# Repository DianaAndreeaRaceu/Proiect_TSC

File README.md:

# InkTime - Hardware Design

## Overview

Acest repository contine partea hardware pentru proiectul InkTime, realizat in Fusion 360 Electronics in jurul microcontroller-ului nRF52840.

Dispozitivul include:
- microcontroller nRF52840
- alimentare din baterie Li-Po
- incarcare prin USB-C
- fuel gauge pentru monitorizarea bateriei
- convertor DC/DC
- display E-Paper
- IMU
- driver haptic
- interfata SWD pentru programare si debug

Scopul proiectului a fost realizarea schemei electrice, a PCB-ului, a fisierelor de fabricatie si a documentatiei tehnice pentru review.

---

## Block Diagram

Diagrama bloc a proiectului este inclusa in folderul Images.

Pe scurt, sistemul functioneaza astfel:
USB-C asigura alimentarea si incarcarea bateriei.
BQ25180 gestioneaza partea de charging si power-path.
RT6160 genereaza rail-ul necesar pentru logica sistemului.
MAX17048 masoara starea bateriei.
nRF52840 este controlerul principal.
Display-ul E-Paper este controlat de microcontroller prin semnale dedicate.
IMU-ul si DRV2605 sunt conectate la MCU prin I2C si GPIO-uri de control.
Antena si reteaua de matching asigura partea RF pentru nRF52840.

---

## Repository Structure

Repository-ul este organizat astfel:

Hardware contine fisierele de schema si PCB.  
Manufacturing contine fisierele Gerber, BOM si CPL.  
Mechanical este rezervat pentru fisiere mecanice, daca este cazul.  
Images contine capturi, randari si diagrama bloc.  
README.md contine documentatia proiectului.  
LICENSE contine licenta open-source.

---

## BOM

Componentele principale folosite in proiect sunt urmatoarele:

Microcontrollerul principal este nRF52840. Acesta gestioneaza toate functiile dispozitivului, inclusiv controlul display-ului, comunicatia cu perifericele, debug-ul si partea RF. Componenta poate fi cautata pe JLCPCB dupa “nRF52840”, iar datasheet-ul oficial este disponibil pe site-ul Nordic Semiconductor.

Circuitul de incarcare si power-path este BQ25180YBGR. Acesta gestioneaza incarcarea bateriei Li-Po si distributia alimentarii in sistem. Componenta poate fi cautata pe JLCPCB dupa “BQ25180”, iar datasheet-ul este disponibil pe site-ul Texas Instruments.

Convertorul DC/DC este RT6160AWSC. Acesta genereaza rail-ul principal de alimentare pentru logica placii. Componenta poate fi cautata pe JLCPCB dupa “RT6160”, iar datasheet-ul este disponibil pe site-ul Richtek.

Fuel gauge-ul este MAX17048G+T10. Acesta monitorizeaza starea bateriei si furnizeaza informatii utile pentru firmware. Componenta poate fi cautata pe JLCPCB dupa “MAX17048”, iar datasheet-ul este disponibil pe site-ul Analog Devices.

IMU-ul folosit este BMA423. Acesta este conectat la microcontroller prin I2C si este folosit pentru detectia miscarii. Componenta poate fi cautata pe JLCPCB dupa “BMA423”, iar datasheet-ul este disponibil pe site-ul Bosch Sensortec.

Driverul haptic este DRV2605YFZR. Acesta controleaza actuatorul de vibratie si este comandat de microcontroller. Componenta poate fi cautata pe JLCPCB dupa “DRV2605”, iar datasheet-ul este disponibil pe site-ul Texas Instruments.

Conectorul USB-C este KH-TYPE-C-16P. Este folosit pentru alimentare si conectivitate USB. Componenta poate fi cautata pe JLCPCB dupa “KH-TYPE-C-16P”, iar datasheet-ul este disponibil pe site-ul furnizorului.

Protectia ESD pentru USB este USBLC6-2SC6Y. Aceasta protejeaza liniile USB impotriva descarcarilor electrostatice. Componenta poate fi cautata pe JLCPCB dupa “USBLC6-2SC6Y”, iar datasheet-ul este disponibil pe site-ul STMicroelectronics.

Conectorul display-ului E-Paper este 503480-2400. Acesta este conectorul principal dintre placa si display. Componenta poate fi cautata pe JLCPCB dupa “503480-2400”, iar datasheet-ul este disponibil pe site-ul Molex.

Antena RF este 2450AT18B100E. Este folosita pentru partea BLE a nRF52840. Componenta poate fi cautata pe JLCPCB dupa “2450AT18B100E”, iar datasheet-ul este disponibil pe site-ul Johanson Technology.

Conectorul SWD este TC2030-IDC. Acesta este folosit pentru programare si debug. Datasheet-ul si documentatia sunt disponibile pe site-ul Tag-Connect.

Cristalul de 32 MHz este folosit ca clock principal RF pentru nRF52840.  
Cristalul de 32.768 kHz este folosit pentru RTC si modul low-power.

In plus, proiectul foloseste:
- rezistente 0201 si 0402 pentru pull-up, configurare, feedback si bias
- condensatoare 0201, 0402 si 0603 pentru decuplare, filtrare, matching RF si charge-pump EPD
- inductoare pentru matching RF si convertorul DC/DC
- diode Schottky si MOSFET-uri in zona de drive a display-ului E-Paper

---

## Hardware Functionality

### Power subsystem

Alimentarea dispozitivului este facuta dintr-o baterie Li-Po, care poate fi incarcata prin USB-C.

Blocurile principale implicate sunt:
- J4, conectorul USB-C
- D3, protectia ESD pentru USB
- IC1, BQ25180
- U3, MAX17048
- IC9, RT6160

VBUS intra prin conectorul USB-C. Liniile USB sunt protejate prin D3. BQ25180 gestioneaza partea de incarcare a bateriei si power-path-ul. MAX17048 monitorizeaza tensiunea si starea bateriei. RT6160 genereaza tensiunea de lucru pentru sistem, adica 3V3.

In aceasta zona sunt importante traseele de alimentare mai late, condensatoarele de decuplare apropiate de pini si mentinerea unei alimentari curate pentru partea digitala si RF.

### MCU si RF

Microcontrollerul folosit este nRF52840. Acesta controleaza display-ul E-Paper, citeste IMU-ul, comanda driverul haptic, comunica cu fuel gauge-ul si charger-ul, permite debug prin SWD si gestioneaza partea RF pentru BLE.

Blocul RF include:
- antena 2450AT18B100E
- reteaua de matching cu inductoare si condensatoare
- cristalul de 32 MHz
- cristalul de 32.768 kHz

Interfetele principale folosite de MCU sunt:
- SPI pentru E-Paper
- I2C pentru IMU, fuel gauge, charger si haptic driver
- SWD pentru programare si debug
- GPIO-uri pentru butoane, reset, busy si interrupt-uri

### E-Paper

Display-ul E-Paper este conectat prin conectorul J1 si printr-un bloc dedicat de drive.

Semnalele principale sunt:
- EPD_CS
- EPD_RST
- EPD_DC
- EPD_BUSY
- MOSI
- SCK

Pe foaia a doua a schemei apare si blocul de drive pentru display, care contine inductoare, diode, MOSFET-uri, rezistente si condensatoare dedicate. Acest bloc genereaza si comuta rail-urile necesare pentru functionarea display-ului.

### IMU

IMU-ul folosit este BMA423.

Acesta este conectat la:
- 3V3
- GND
- SDA
- SCL
- un pin de interrupt catre MCU

Rolul lui este detectia miscarii si suportul pentru functii low-power sau evenimente bazate pe miscare.

### Haptic driver

Driverul haptic este DRV2605.

Acesta este conectat la:
- alimentare
- GND
- magistrala I2C
- un semnal de control / enable
- iesirea catre actuatorul haptic

Rolul lui este generarea de feedback prin vibratie.

### Buttons

Placa include trei butoane:
- SW_UP
- SW_ENT
- SW_DN

Fiecare buton are rezistenta de pull-up si condensator de filtrare/debouncing. Butoanele sunt conectate la GPIO-uri dedicate ale microcontrollerului.

### Debug si test

Pentru programare, testare si debugging sunt disponibile:
- J2, conectorul SWD
- test pads pentru SWDIO, SWDCLK, RESET, SWO, 3V3, GND, SDA, SCL, VREG, VBAT si iesirile driverului haptic

Acest lucru ajuta la bring-up si depanare dupa asamblarea placii.

---

## nRF52840 Pin Usage

Semnalele importante conectate la nRF52840 sunt urmatoarele:

Pinii XL1 si XL2 sunt folositi pentru cristalul de 32.768 kHz, necesar pentru RTC si modurile low-power.

Pinii XC1 si XC2 sunt folositi pentru cristalul de 32 MHz, necesar pentru functionarea precisa a blocului RF.

Pinul ANT este conectat la reteaua de matching si apoi la antena, pentru comunicatia BLE.

Semnalele SWDIO si SWDCLK sunt scoase la conectorul J2 si la test pads, pentru programare si debug.

Semnalul RESET este scos la headerul de debug si la test pad pentru reset extern.

Semnalele EPD_CS, EPD_RST, EPD_DC si EPD_BUSY sunt folosite pentru controlul display-ului E-Paper.

Semnalele SCK si MOSI sunt folosite pentru comunicatia SPI cu display-ul.

Semnalele SDA si SCL sunt folosite ca magistrala I2C comuna pentru IMU, fuel gauge, charger si haptic driver.

Semnalul IMU_INT este folosit pentru intreruperi de la BMA423.

Semnalul PMIC_INT este folosit pentru semnalizarea evenimentelor charger/PMIC.

Semnalul HAPTIC_EN este folosit pentru controlul driverului haptic.

Semnalele SW_UP, SW_ENT si SW_DN sunt folosite pentru interfata cu utilizatorul.

Semnalul ALERT este folosit pentru evenimente de la fuel gauge.

Semnalele de enable pentru partea EPD sunt folosite pentru controlul alimentarii display-ului.

Pinii au fost alesi astfel incat:
- pinii dedicati de debug sa ramana disponibili pentru SWD
- pinii dedicati cristalelor sa fie folositi conform functiei lor
- semnalele SPI sa fie grupate logic
- I2C-ul sa fie folosit ca magistrala comuna pentru periferice low-speed
- GPIO-urile simple sa fie folosite pentru butoane si interrupt-uri

---

## Communication Interfaces

Interfetele folosite in proiect sunt:
- SPI intre nRF52840 si display-ul E-Paper
- I2C intre nRF52840 si BMA423, MAX17048, BQ25180 si DRV2605
- SWD intre nRF52840 si headerul J2
- GPIO pentru butoane si semnale de control

---

## Energy and Power Considerations

Consumul exact depinde de firmware si de duty-cycle, dar hardware-ul este proiectat pentru un sistem portabil pe baterie.

Sursele principale de consum sunt:
- nRF52840
- refresh-ul display-ului E-Paper
- driverul haptic in timpul vibratiei
- fuel gauge-ul si PMIC-ul
- IMU-ul in mod activ sau low-power

Observatii importante:
- E-Paper consuma in principal in timpul refresh-ului, nu in afisare statica
- IMU-ul poate functiona in mod low-power
- fuel gauge-ul are consum mic, dar permanent
- BLE si activitatea MCU influenteaza puternic autonomia

Pentru o baterie de capacitate C_bat in mAh si un curent mediu estimat I_avg in mA, autonomia teoretica se poate aproxima cu relatia:

T = C_bat / I_avg

Exemplu:
Pentru o baterie de 150 mAh si un consum mediu de 3 mA, autonomia estimata este de aproximativ 50 de ore.

Aceasta este doar o estimare orientativa. Consumul real depinde de frecventa refresh-ului E-Paper, activitatea BLE, utilizarea vibratorului si strategia de citire a senzorilor.

---

## PCB Design Notes

PCB-ul a fost realizat pe doua straturi.

Deciziile principale de layout au fost:
- MCU-ul si zona RF au fost plasate in partea dreapta-sus
- conectorul E-Paper si blocul sau de drive au fost grupate in partea stanga
- butoanele au fost plasate pe marginea inferioara
- USB-C este pe muchia superioara
- test pads-urile au fost plasate in zone accesibile pentru debugging

Observatii:
- antena este tinuta la marginea placii
- matching network-ul este plasat intre MCU si antena
- decuplarile sunt distribuite in jurul blocurilor active
- PCB-ul este in stadiul livrabil pentru review si verificare

---

## Design Log

Problemele principale intalnite au fost:
- organizarea componentelor pe o placa mica
- densitatea mare in jurul nRF52840
- rutarea in zona RF si in zona de power
- pozitionarea test pads-urilor fara a bloca rutarea

Modificari facute dupa review:
- componentele au fost mutate in interiorul conturului placii
- placement-ul a fost reorganizat pe blocuri functionale
- au fost generate fisierele de fabricatie: Gerber, BOM si CPL
- documentatia a fost completata cu BOM si descriere hardware

---

## Manufacturing Outputs

Repository-ul include 
:
- gerbers.zip
- bom.csv
- cpl.csv

Aceste fisiere permit fabricarea PCB-ului, asamblarea automata si verificarea componentelor si footprint-urilor.

---

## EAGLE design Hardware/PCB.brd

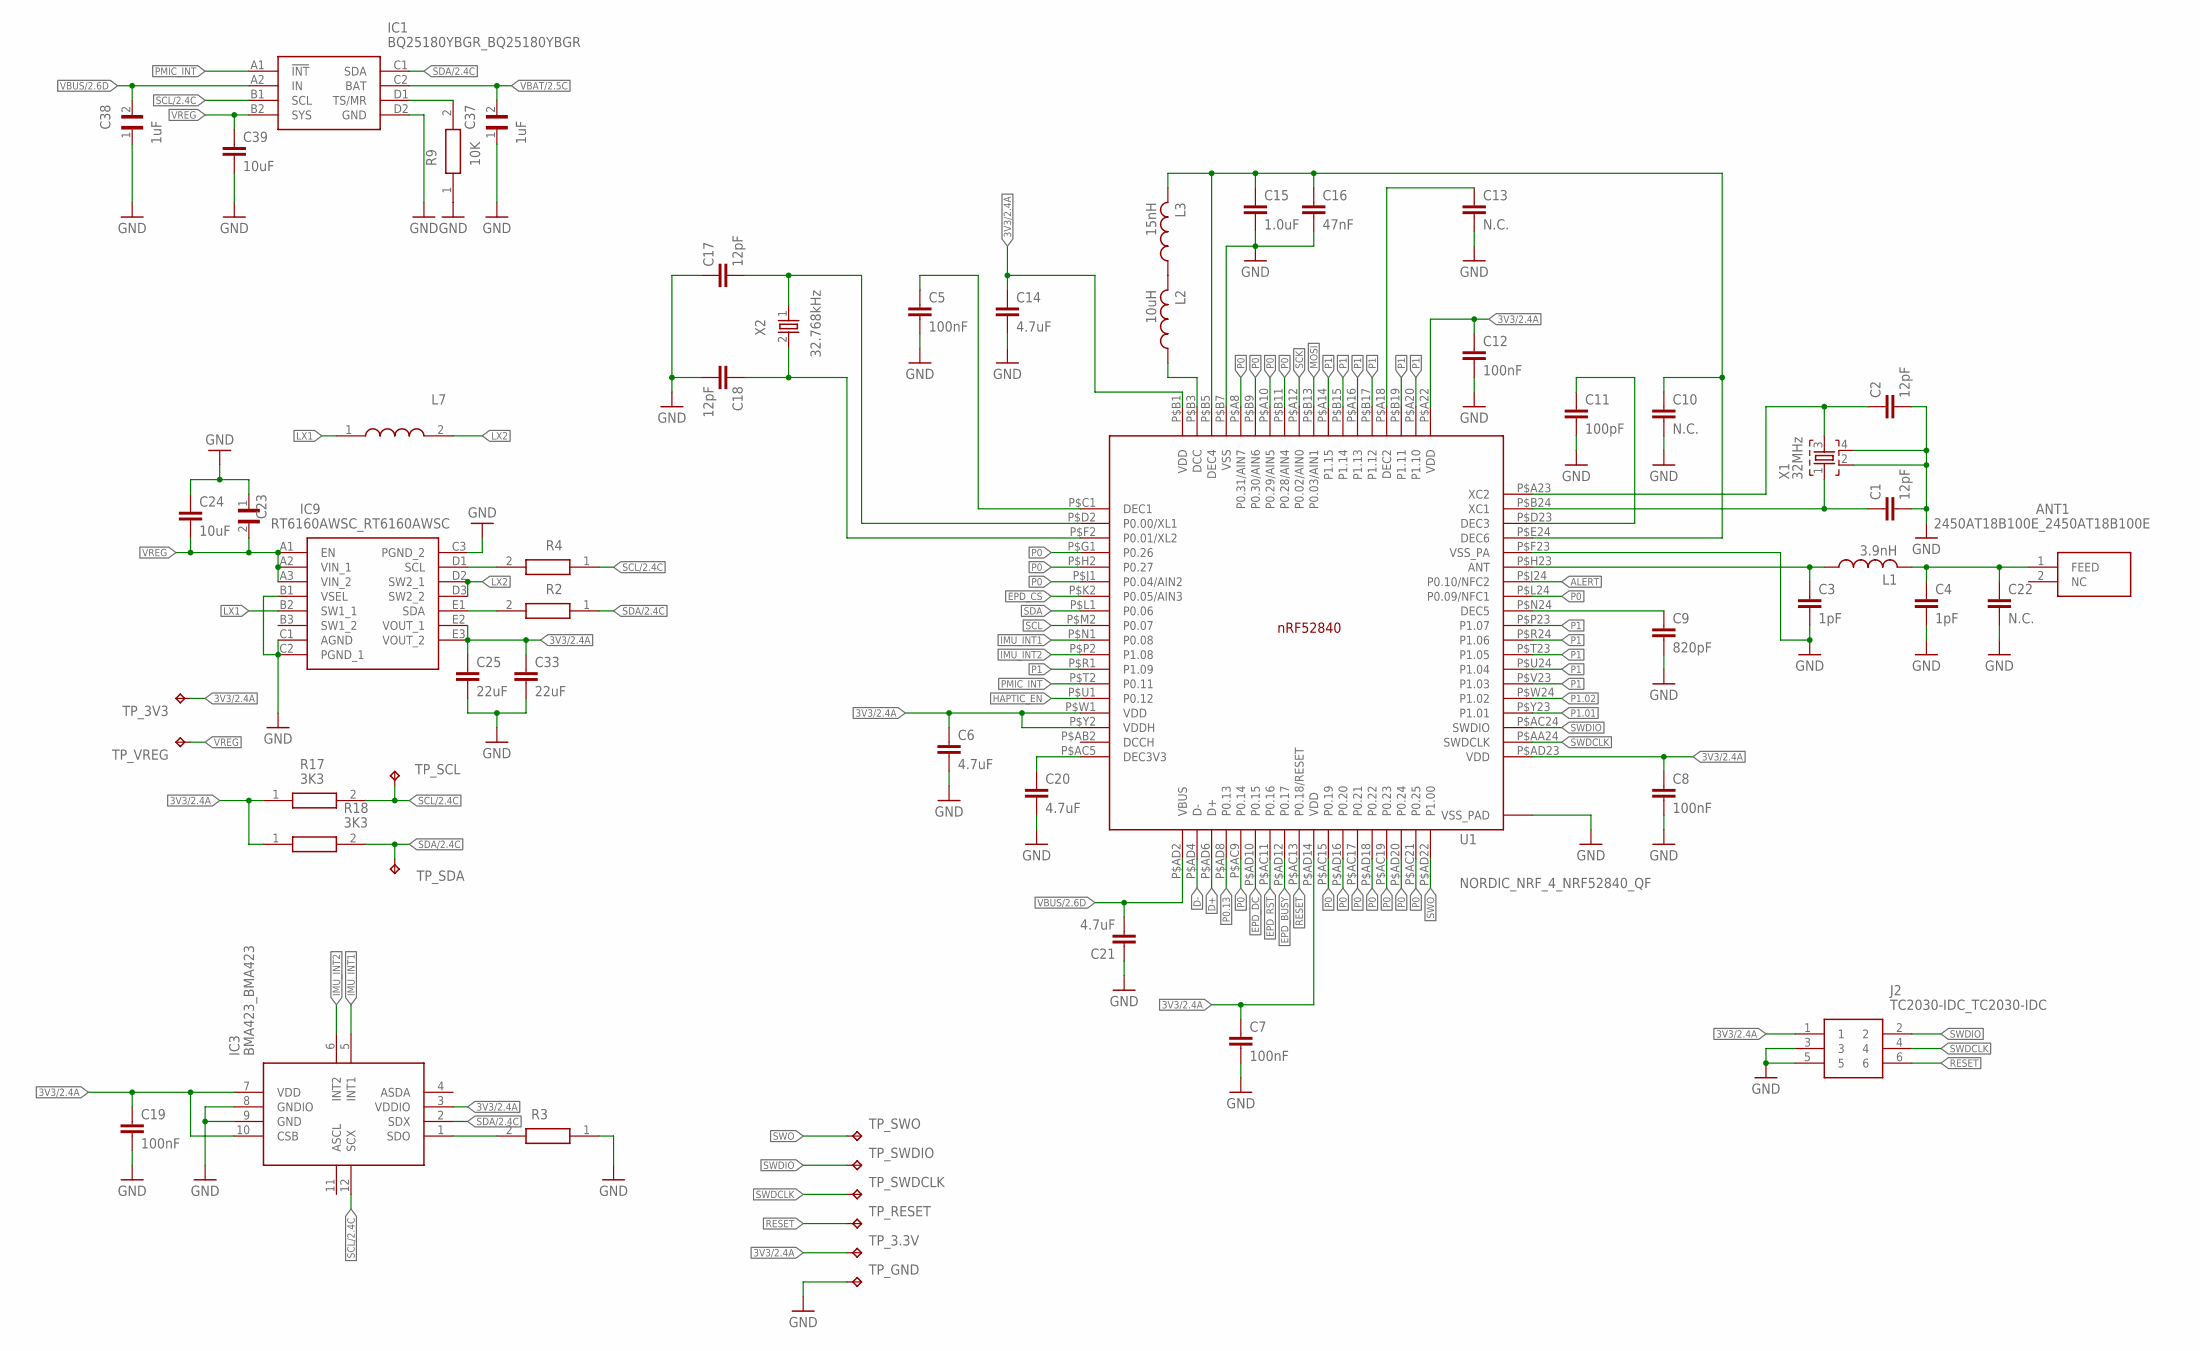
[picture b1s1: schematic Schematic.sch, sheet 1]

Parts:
ANT1: 2450AT18B100E_2450AT18B100E; 2450AT18B100E_ANTC3216X140N
C1, C2, C17, C18: 12pF; NORDIC_NRF_3_RESC0201_N
C3, C4: 1pF; NORDIC_NRF_3_RESC0201_N
C5, C7, C8, C12, C19: 100nF; NORDIC_NRF_3_RESC0201_N
C6, C14, C20, C21: 4.7uF; NORDIC_NRF_3_RESC0402_N
C9: 820pF; NORDIC_NRF_3_RESC0201_N
C10, C13, C22: N.C.; PERFECT_0402_0402
C11: 100pF; NORDIC_NRF_3_RESC0201_N
C15: 1.0uF; NORDIC_NRF_3_RESC0402_N
C16: 47nF; NORDIC_NRF_3_RESC0201_N
C23: GRM011R60J152KE01L_2_GRM011R60J152KE01L; GRM011R60J152KE01L_2_CAPC0201X13N
C24, C39: 10uF; NORDIC_NRF_3_RESC0402_N
C25, C33: 22uF; NORDIC_NRF_3_RESC0402_N
C37, C38: 1uF; GRM011R60J152KE01L_2_CAPC0201X13N
IC1: BQ25180YBGR_BQ25180YBGR; BQ25180YBGR_BGA8C40P2X4_100X155X50
IC3: BMA423_BMA423
IC9: RT6160AWSC_RT6160AWSC; RT6160AWSC_BGA15C40P3X5_140X230X60
J2: TC2030-IDC_TC2030-IDC; TC2030-IDC_TC2030IDC
L1: 3.9nH; NORDIC_NRF_2_RESC0402_L
L2: 10uH; NORDIC_NRF_2_RESC0402_L
L3: 15nH; NORDIC_NRF_2_RESC0402_L
L7: MLP2016SR47MT0S1_FTC252012SR47MBCA; MLP2016SR47MT0S1_INDC2016X100N
R2, R3: CPF0201D7K68C1_CPF0201D7K68C1; CPF0201D7K68C1_0201
R4: 0; CPF0201D7K68C1_0201
R9: 10K; CPF0201D7K68C1_0201
R17, R18: 3K3; CPF0201D7K68C1_0201
TP_3.3V, TP_3V3: HECTOR_WATCH_1_TPTP20R; HECTOR_WATCH_1_TP20R
TP_GND: HECTOR_WATCH_1_TPTP20R; HECTOR_WATCH_1_TP20R
TP_RESET: HECTOR_WATCH_1_TPTP20R; HECTOR_WATCH_1_TP20R
TP_SCL: HECTOR_WATCH_1_TPTP20R; HECTOR_WATCH_1_TP20R
TP_SDA: HECTOR_WATCH_1_TPTP20R; HECTOR_WATCH_1_TP20R
TP_SWDCLK: HECTOR_WATCH_1_TPTP20R; HECTOR_WATCH_1_TP20R
TP_SWDIO: HECTOR_WATCH_1_TPTP20R; HECTOR_WATCH_1_TP20R
TP_SWO: HECTOR_WATCH_1_TPTP20R; HECTOR_WATCH_1_TP20R
TP_VREG: HECTOR_WATCH_1_TPTP20R; HECTOR_WATCH_1_TP20R
U1: NORDIC_NRF_4_NRF52840_QF; NORDIC_NRF_4_AQFN50P700X700X85_HS-74N
X1: 32MHz; NORDIC_NRF_BT-XTAL_2016_N
X2: 32.768kHz; NORDIC_NRF_1_XTAL_3215_N

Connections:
3V3/2.4A: C6.1, C7.1, C8.1, C12.1, C14.1, C19.1, C25.1, C33.1, IC3.3 (VDDIO), IC3.7 (VDD), IC3.10 (CSB), IC9.E2 (VOUT_1), IC9.E3 (VOUT_2), J2.1, R17.1, R18.1, TP_3.3V.TP, TP_3V3.TP, U1.P$A22 (VDD), U1.P$AD14 (VDD), U1.P$AD23 (VDD), U1.P$B1 (VDD), U1.P$W1 (VDD), U1.P$Y2 (VDDH)
D-: U1.P$AD4 (D-); also elsewhere on the board
GND: C1.2, C2.2, C3.2, C4.2, C5.2, C6.2, C7.2, C8.2, C9.2, C10.2, C11.2, C12.2, C13.2, C14.2, C15.2, C16.2, C17.1, C18.2, C19.2, C20.2, C21.1, C22.2, C23.1, C24.1, C25.2, C33.2, C37.1, C38.1, C39.2, IC1.D2 (GND), IC3.8 (GNDIO), IC3.9 (GND), IC9.B1 (VSEL), IC9.C1 (AGND), IC9.C2 (PGND_1), IC9.C3 (PGND_2), J2.3, J2.5, R3.1, R9.1, TP_GND.TP, U1.P$74 (VSS_PAD), U1.P$75 (VSS_PAD), U1.P$76 (VSS_PAD), U1.P$77 (VSS_PAD), U1.P$78 (VSS_PAD), U1.P$79 (VSS_PAD), U1.P$80 (VSS_PAD), U1.P$81 (VSS_PAD), U1.P$82 (VSS_PAD), U1.P$83 (VSS_PAD), U1.P$84 (VSS_PAD), U1.P$85 (VSS_PAD), U1.P$86 (VSS_PAD), U1.P$87 (VSS_PAD), U1.P$88 (VSS_PAD), U1.P$89 (VSS_PAD), U1.P$90 (VSS_PAD), U1.P$B7 (VSS), U1.P$F23 (VSS_PA), X1.2, X1.4; also elsewhere on the board
HAPTIC_EN: U1.P$U1 (P0.12); also elsewhere on the board
IMU_INT1: IC3.5 (INT1)
IMU_INT2: IC3.6 (INT2)
LX1: IC9.B2 (SW1_1), L7.1
LX2: IC9.D2 (SW2_1), IC9.D3 (SW2_2), L7.2
unnamed: C5.1, U1.P$C1 (DEC1)
unnamed: IC9.D1 (SCL), R4.2
unnamed: IC3.1 (SDO), R3.2
unnamed: IC9.E1 (SDA), R2.2
unnamed: IC1.D1 (TS/MR), R9.2
unnamed: C20.1, U1.P$AC5 (DEC3V3)
unnamed: L2.1, U1.P$B3 (DCC)
unnamed: L2.2, L3.1
unnamed: C10.1, C15.1, C16.1, L3.2, U1.P$B5 (DEC4), U1.P$E24 (DEC6)
unnamed: C13.1, U1.P$A18 (DEC2)
unnamed: C17.2, U1.P$D2 (P0.00/XL1), X2.1
unnamed: C18.1, U1.P$F2 (P0.01/XL2), X2.2
unnamed: C9.1, U1.P$N24 (DEC5)
unnamed: C11.1, U1.P$D23 (DEC3)
unnamed: C2.1, U1.P$A23 (XC2), X1.3
unnamed: C1.1, U1.P$B24 (XC1), X1.1
unnamed: ANT1.1 (FEED), C4.1, C22.1, L1.2
unnamed: C3.1, L1.1, U1.P$H23 (ANT)
P0: U1.P$A8 (P0.31/AIN7)
PMIC_INT: IC1.A1 (!INT)
RESET: J2.6, TP_RESET.TP
SCL/2.4C: IC1.B1 (SCL), IC3.12 (SCX), R4.1, R17.2, TP_SCL.TP
SDA/2.4C: IC1.C1 (SDA), IC3.2 (SDX), R2.1, R18.2, TP_SDA.TP
SWDCLK: J2.4, TP_SWDCLK.TP, U1.P$AA24 (SWDCLK)
SWDIO: J2.2, TP_SWDIO.TP
SWO: TP_SWO.TP, U1.P$AD22 (P1.00)
VBAT/2.5C: C37.2, IC1.C2 (BAT)
VBUS/2.6D: C21.2, C38.2, IC1.A2 (IN), U1.P$AD2 (VBUS)
VREG: C23.2, C24.2, C39.1, IC1.B2 (SYS), IC9.A1 (EN), IC9.A2 (VIN_1), IC9.A3 (VIN_2), TP_VREG.TP

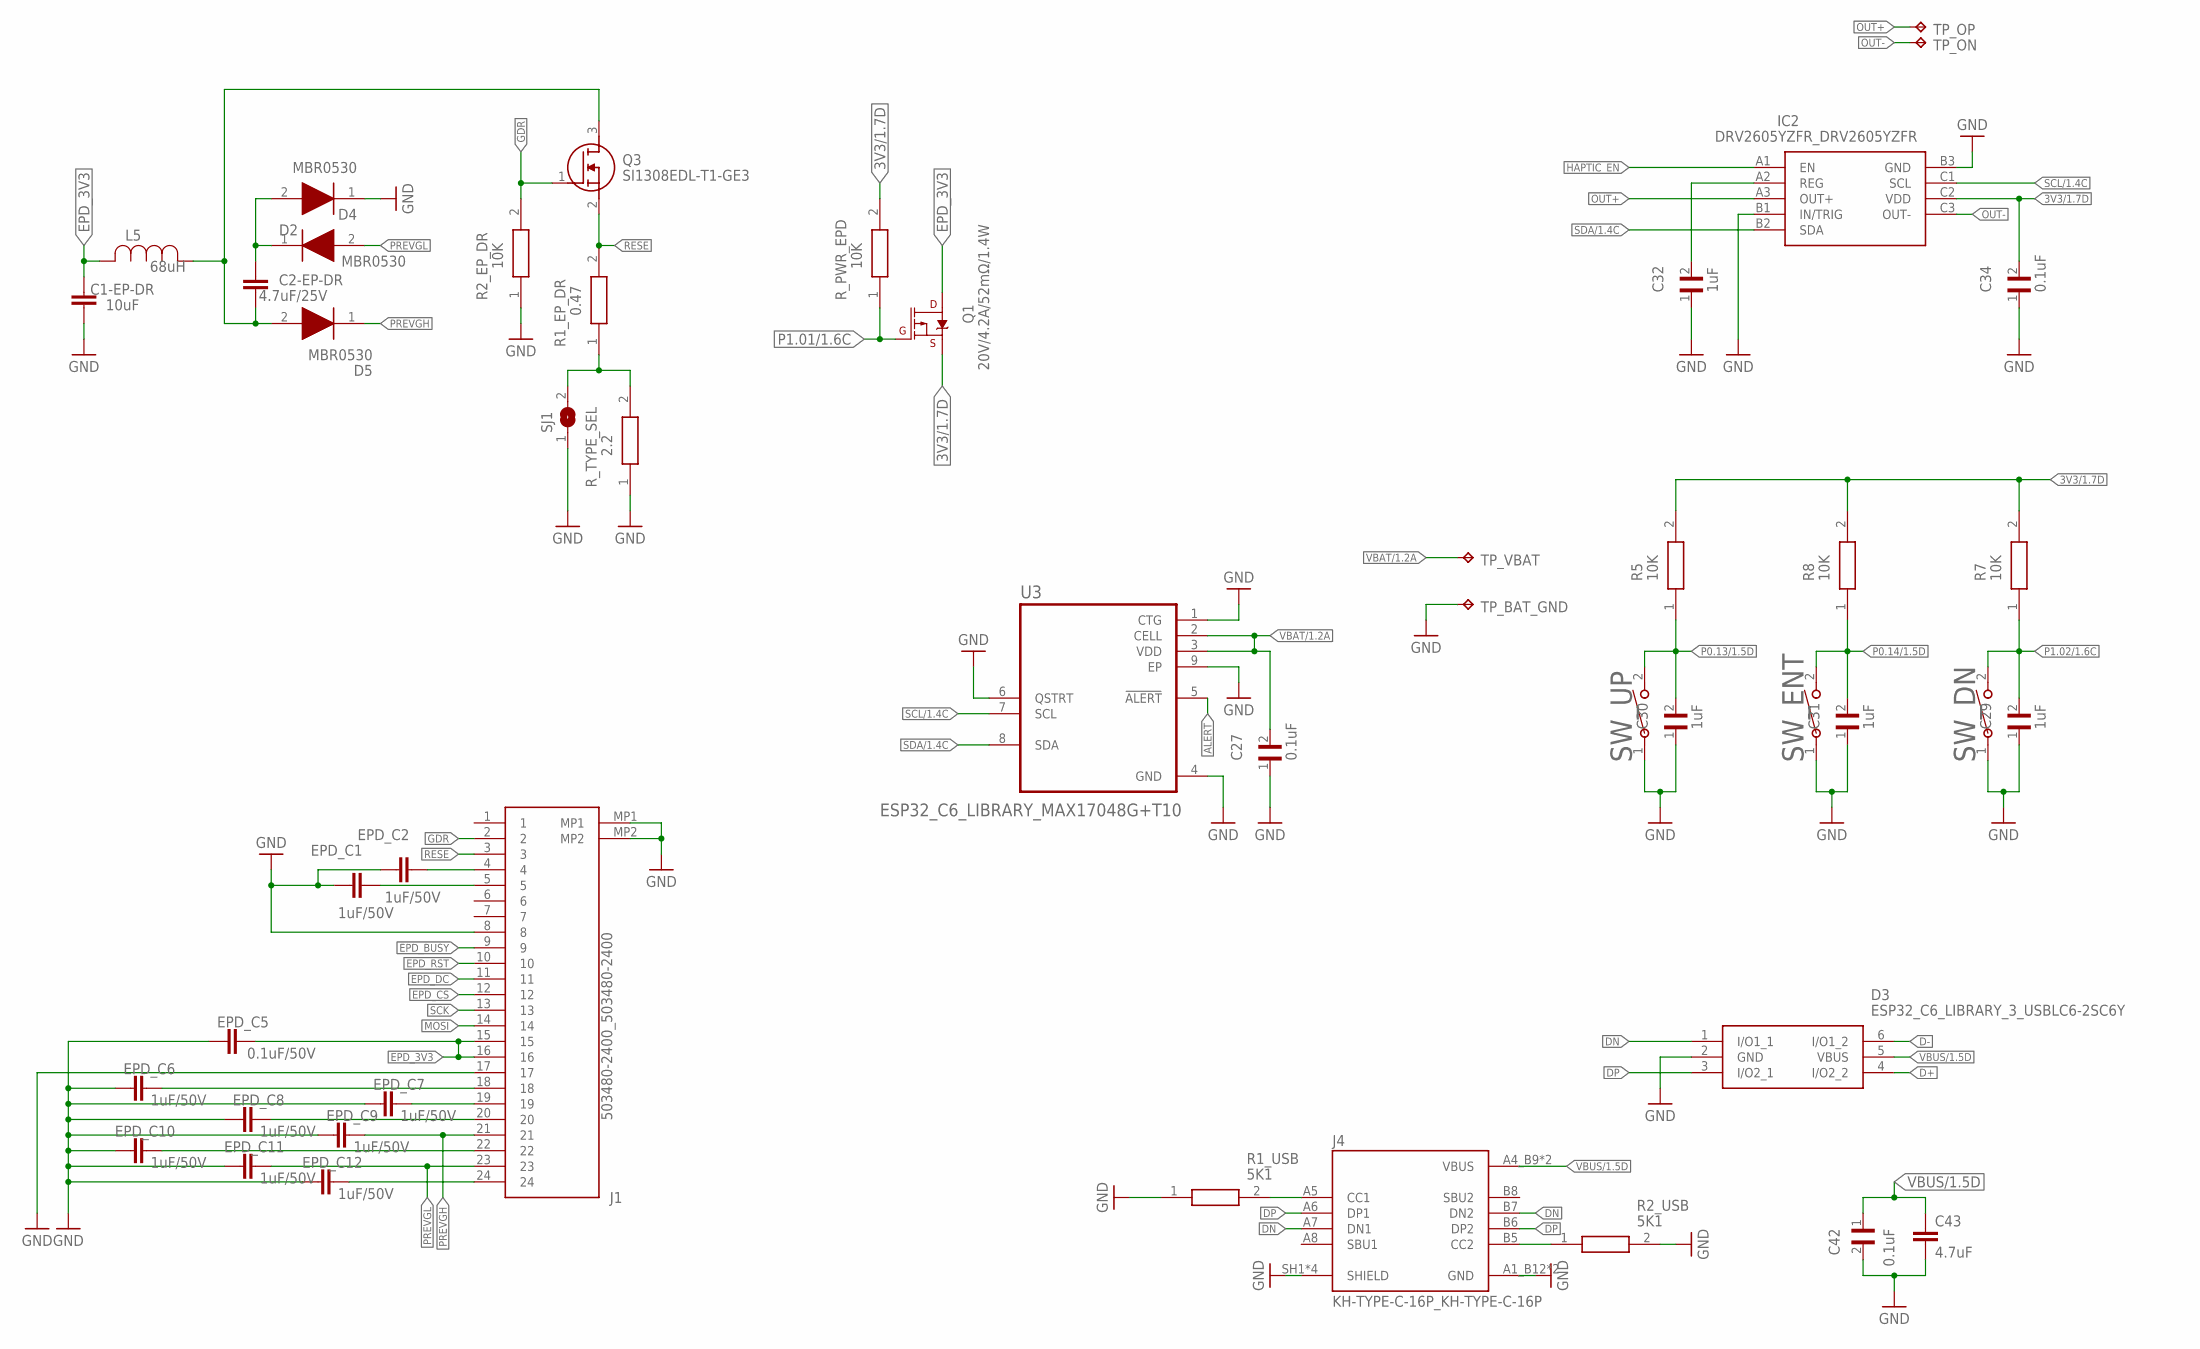
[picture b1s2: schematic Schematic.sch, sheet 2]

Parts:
C1-EP-DR: 10uF; NORDIC_NRF_3_RESC0402_N
C2-EP-DR: 4.7uF/25V; NORDIC_NRF_3_RESC0402_N
C27, C34, C42: 0.1uF; GRM011R60J152KE01L_2_CAPC0201X13N
C29, C30, C31, C32: 1uF; GRM011R60J152KE01L_2_CAPC0201X13N
C43: 4.7uF; NORDIC_NRF_3_RESC0402_N
D2, D4, D5: MBR0530; ESP32_C6_LIBRARY_5_SOD3716X135N
D3: ESP32_C6_LIBRARY_3_USBLC6-2SC6Y; ESP32_C6_LIBRARY_3_SOT95P280X145-6N
EPD_C1, EPD_C2, EPD_C6, EPD_C7, EPD_C8, EPD_C9, EPD_C10, EPD_C11, EPD_C12: 1uF/50V; NORDIC_NRF_3_RESC0402_N
EPD_C5: 0.1uF/50V; NORDIC_NRF_3_RESC0402_N
IC2: DRV2605YZFR_DRV2605YZFR; DRV2605YZFR_BGA9C50P3X3_144X144X62
J1: 503480-2400_503480-2400; 503480-2400_5034802400
J4: KH-TYPE-C-16P_KH-TYPE-C-16P; KH-TYPE-C-16P_KINGHELM_KH-TYPE-C-16P
L5: 68uH; ESP32_C6_LIBRARY_2_IND_4828-WE-TPC_WRE
Q1: 20V/4.2A/52mΩ/1.4W; ESP32_C6_LIBRARY_4_ESP32_C6_LIBRARY_4_ESP32_C6_LIBRARY_4_ES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
Q3: SI1308EDL-T1-GE3; ESP32_C6_LIBRARY_6_SOT65P210X110-3N
R1_EP_DR: 0.47; CPF0201D7K68C1_0201
R1_USB, R2_USB: 5K1; CPF0201D7K68C1_0201
R2_EP_DR, R5, R7, R8: 10K; CPF0201D7K68C1_0201
R_PWR_EPD: 10K; CPF0201D7K68C1_0201
R_TYPE_SEL: 2.2; CPF0201D7K68C1_0201
SJ1: ESP32_C6_LIBRARY_7_JUMPER_SJ
SW_DN: 2025-10-22_07-23-44_LIBRARY_EVP-AKE31ASW_EVP-AKE3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; 2025-10-22_07-23-44_LIBRARY_SW_EVP-AKE31A_PAN
SW_ENT: 2025-10-22_07-23-44_LIBRARY_EVP-AKE31ASW_EVP-AKE3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; 2025-10-22_07-23-44_LIBRARY_SW_EVP-AKE31A_PAN
SW_UP: 2025-10-22_07-23-44_LIBRARY_EVP-AKE31ASW_EVP-AKE3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; 2025-10-22_07-23-44_LIBRARY_SW_EVP-AKE31A_PAN
TP_BAT_GND: HECTOR_WATCH_1_TPTP20R; HECTOR_WATCH_1_TP20R
TP_ON: HECTOR_WATCH_1_TPTP20R; HECTOR_WATCH_1_TP20R
TP_OP: HECTOR_WATCH_1_TPTP20R; HECTOR_WATCH_1_TP20R
TP_VBAT: HECTOR_WATCH_1_TPTP20R; HECTOR_WATCH_1_TP20R
U3: ESP32_C6_LIBRARY_MAX17048G+T10; ESP32_C6_LIBRARY_SON50P200X200X80-9N

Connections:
3V3/1.7D: C34.2, IC2.C2 (VDD), Q1.2 (S), R5.2, R7.2, R8.2, R_PWR_EPD.2
ALERT: U3.5 (!ALERT)
D+: D3.4 (I/O2_2)
D-: D3.6 (I/O1_2); also elsewhere on the board
DN: D3.1 (I/O1_1), J4.B7 (DN2)
DP: D3.3 (I/O2_1), J4.A6 (DP1), J4.B6 (DP2)
EPD_3V3: C1-EP-DR.2, EPD_C5.2, J1.15, J1.16, L5.2, Q1.3 (D)
EPD_BUSY: J1.9
EPD_CS: J1.12
EPD_DC: J1.11
EPD_RST: J1.10
GDR: J1.2, Q3.1 (G), R2_EP_DR.2
GND: C1-EP-DR.1, C27.1, C29.1, C30.1, C31.1, C32.1, C34.1, C42.2, C43.2, D3.2 (GND), D4.1 (K), EPD_C1.1, EPD_C2.1, EPD_C5.1, EPD_C6.1, EPD_C7.1, EPD_C8.1, EPD_C9.1, EPD_C10.1, EPD_C11.1, EPD_C12.1, IC2.B1 (IN/TRIG), IC2.B3 (GND), J1.8, J1.17, J1.MP1, J1.MP2, J4.A1_B12 (GND), J4.A12_B1 (GND), J4.SH1 (SHIELD), J4.SH2 (SHIELD), J4.SH3 (SHIELD), J4.SH4 (SHIELD), R1_USB.1, R2_EP_DR.1, R2_USB.2, R_TYPE_SEL.1, SJ1.1, SW_DN.1, SW_ENT.1, SW_UP.1, TP_BAT_GND.TP, U3.1 (CTG), U3.4 (GND), U3.6 (QSTRT), U3.9 (EP); also elsewhere on the board
HAPTIC_EN: IC2.A1 (EN); also elsewhere on the board
MOSI: J1.14
unnamed: C31.2, R8.1, SW_ENT.2
unnamed: C30.2, R5.1, SW_UP.2
unnamed: J4.B5 (CC2), R2_USB.1
unnamed: J4.A5 (CC1), R1_USB.2
unnamed: EPD_C2.2, J1.4
unnamed: C32.2, IC2.A2 (REG)
unnamed: C2-EP-DR.2, D5.2 (A), L5.1, Q3.3 (D)
unnamed: EPD_C1.2, J1.5
unnamed: EPD_C7.2, J1.19
unnamed: R1_EP_DR.1, R_TYPE_SEL.2, SJ1.2
unnamed: EPD_C12.2, J1.24
unnamed: EPD_C8.2, J1.20
unnamed: EPD_C6.2, J1.18
unnamed: EPD_C10.2, J1.22
unnamed: C2-EP-DR.1, D2.1 (K), D4.2 (A)
OUT+: IC2.A3 (OUT+), TP_OP.TP
OUT-: IC2.C3 (OUT-), TP_ON.TP
P1.01/1.6C: Q1.1 (G), R_PWR_EPD.1
P1.02/1.6C: C29.2, R7.1, SW_DN.2
PREVGH: D5.1 (K), EPD_C9.2, J1.21
PREVGL: D2.2 (A), EPD_C11.2, J1.23
RESE: J1.3, Q3.2 (S), R1_EP_DR.2
SCK: J1.13
SCL/1.4C: IC2.C1 (SCL), U3.7 (SCL)
SDA/1.4C: IC2.B2 (SDA), U3.8 (SDA)
VBAT/1.2A: C27.2, TP_VBAT.TP, U3.2 (CELL), U3.3 (VDD)
VBUS/1.5D: C42.1, C43.1, D3.5 (VBUS), J4.A4_B9 (VBUS), J4.A9_B4 (VBUS)

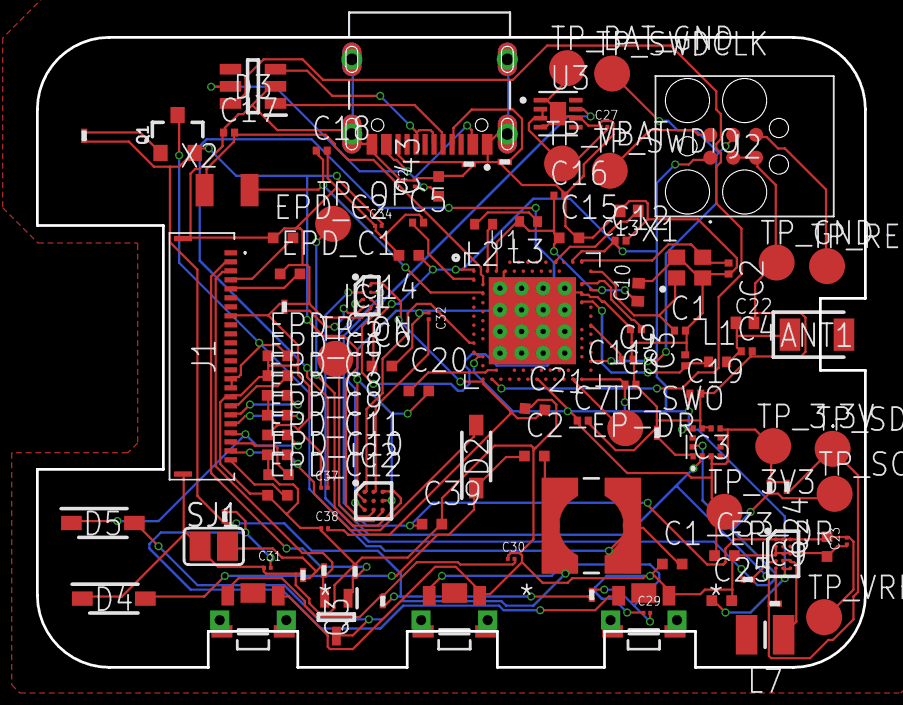
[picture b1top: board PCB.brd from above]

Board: 2 copper layers, 46.0 x 35.0 mm, 105 parts (0 on the bottom side), 64 nets.

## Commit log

2026-04-18 Create LICENSE
2026-04-18 Reorganize repository and add project deliverables
2026-04-18 Remove DS_Store and fix repository filenames
2026-04-18 Add Mechanical folder placeholder
2026-04-18 Rename Readme.md to README.md
2026-04-21 Update repository

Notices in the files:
parts and their libraries:
COPYRIGHT: Copyright (C) 2024 Ultra Librarian. All rights reserved.
COPYRIGHT: Copyright (C) 2025 Ultra Librarian. All rights reserved.
